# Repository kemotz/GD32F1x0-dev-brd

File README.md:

# GD32F1x0-dev-brd
 
GigaDevice GD32F1x0 value line MCU development board. The board supports F130/150/170/190 however the assembly files are created for F190 using JLCPCB service.

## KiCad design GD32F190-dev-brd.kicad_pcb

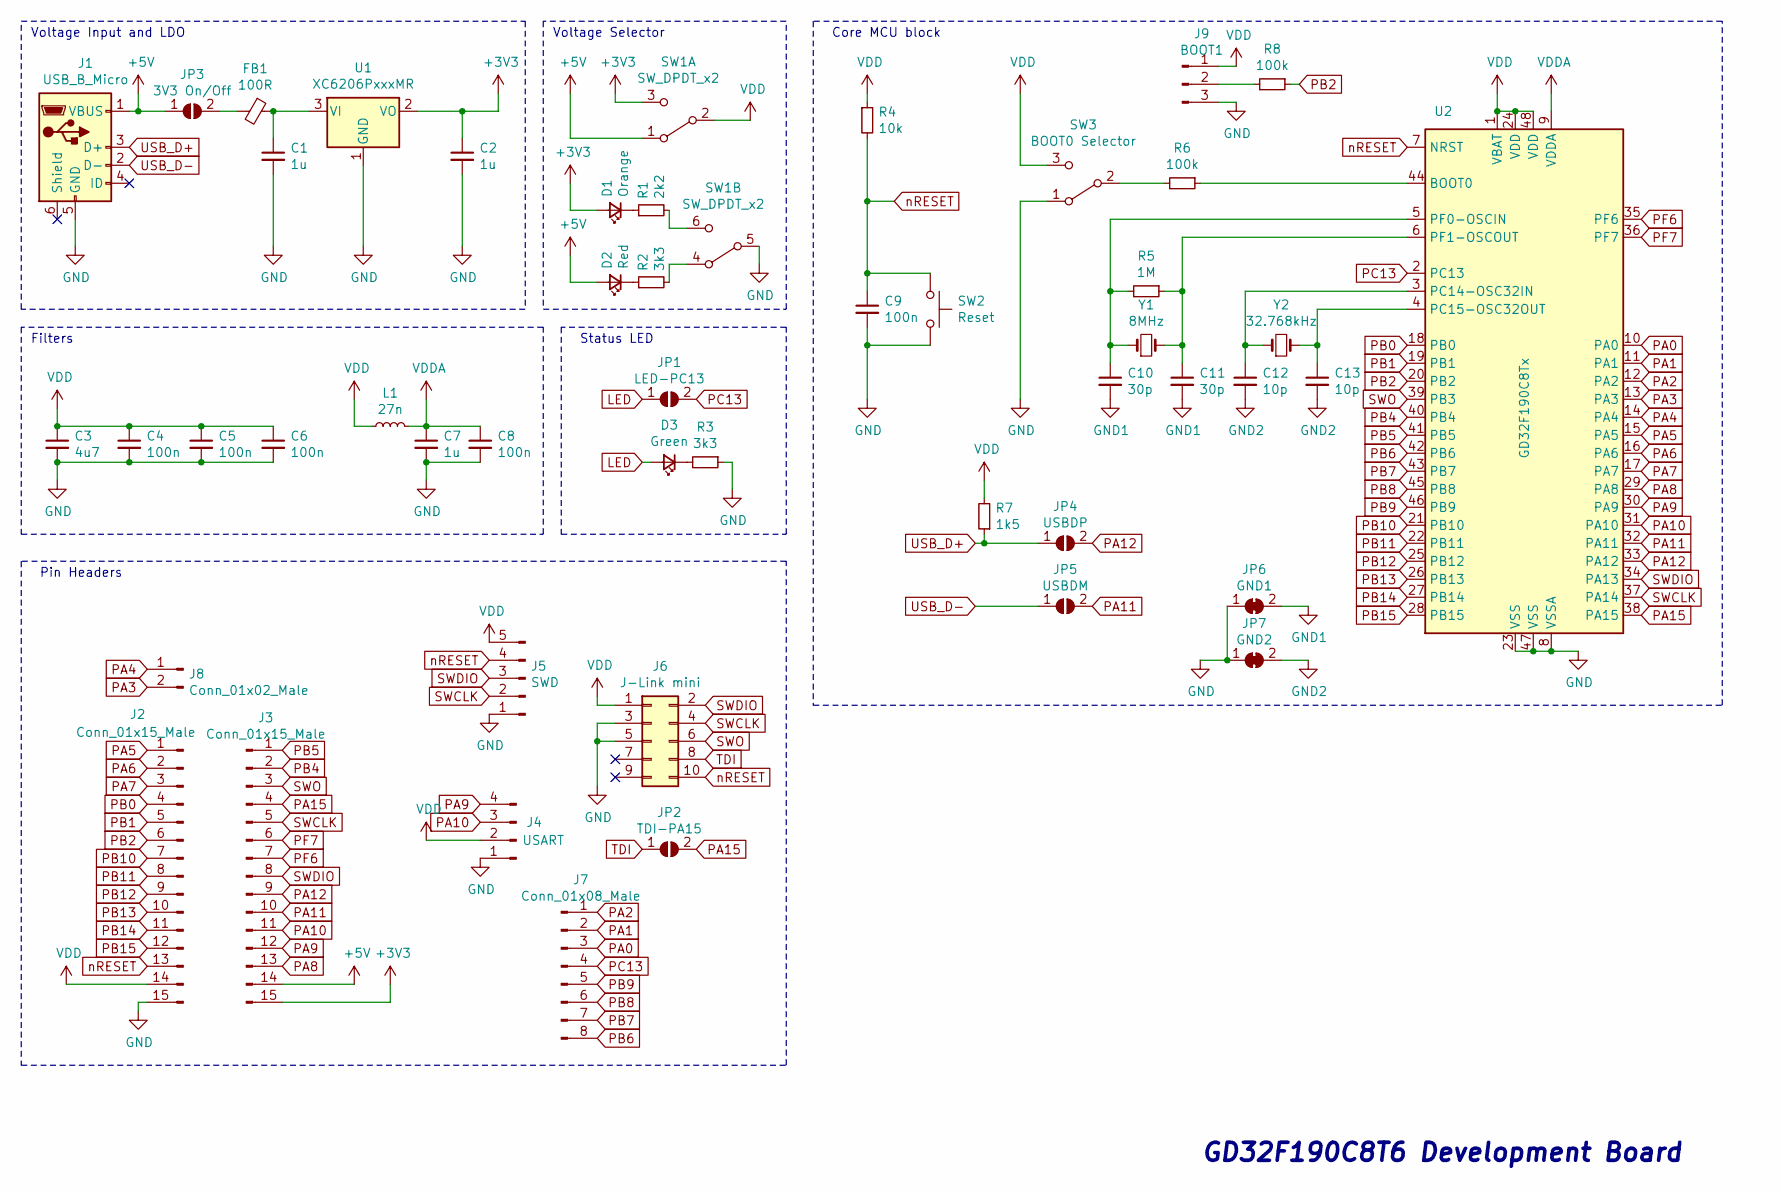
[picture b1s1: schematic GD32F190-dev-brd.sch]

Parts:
C1, C2, C7: 1u; C_0603_1608Metric
C3: 4u7; C_0402_1005Metric
C4, C5, C6: 100n; C_0402_1005Metric
C8, C9: 100n; C_0603_1608Metric
C10, C11: 30p; C_0603_1608Metric
C12, C13: 10p; C_0603_1608Metric
D1: Orange; LED_0603_1608Metric
D2: Red; LED_0603_1608Metric
D3: Green; LED_0603_1608Metric
FB1: 100R; L_0805_2012Metric
J1: USB_B_Micro; USB_Micro-B_MicroQTJ
J2, J3: Conn_01x15_Male; PinHeader_1x15_P2.54mm_Vertical
J4: USART; PinHeader_1x04_P2.54mm_Vertical
J5: SWD; PinHeader_1x05_P2.54mm_Vertical
J6: J-Link mini; PinHeader_2x05_P1.27mm_Vertical
J7: Conn_01x08_Male; PinHeader_1x08_P2.54mm_Vertical
J8: Conn_01x02_Male; PinHeader_1x02_P2.54mm_Vertical
J9: BOOT1; PinHeader_1x03_P2.54mm_Vertical
JP1: LED-PC13; SolderJumper-2_P1.3mm_Open_RoundedPad1.0x1.5mm
JP2: TDI-PA15; SolderJumper-2_P1.3mm_Open_RoundedPad1.0x1.5mm
JP3: 3V3 On/Off; SolderJumper-2_P1.3mm_Open_RoundedPad1.0x1.5mm
JP4: USBDP; SolderJumper-2_P1.3mm_Open_RoundedPad1.0x1.5mm
JP5: USBDM; SolderJumper-2_P1.3mm_Open_RoundedPad1.0x1.5mm
JP6: GND1; GND-bridge
JP7: GND2; GND-bridge
L1: 27n; L_0603_1608Metric
R1: 2k2; R_0603_1608Metric
R2, R3: 3k3; R_0603_1608Metric
R4: 10k; R_0603_1608Metric
R5: 1M; R_0603_1608Metric
R6, R8: 100k; R_0603_1608Metric
R7: 1k5; R_0603_1608Metric
SW1: SW_DPDT_x2; SK22H03
SW2: Reset; SW_SPST_PTS810
SW3: BOOT0 Selector; SK22H03
U1: XC6206PxxxMR; SOT-23
U2: GD32F190C8Tx; LQFP-48_7x7mm_P0.5mm
Y1: 8MHz; Crystal_SMD_5032-2Pin_5.0x3.2mm
Y2: 32.768kHz; Crystal_SMD_3215-2Pin_3.2x1.5mm

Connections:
+3V3: C2.1, D1.2 (A), J3.15, SW1.3 (C), U1.2 (VO)
+5V: D2.2 (A), J1.1 (VBUS), J3.14, JP3.1 (A), SW1.1 (A)
GND: C1.2, C2.2, C3.2, C4.2, C5.2, C6.2, C7.2, C8.2, C9.2, J1.5 (GND), J2.15, J4.1, J5.1, J6.3, J6.5, J9.3, JP6.1 (A), JP7.1 (A), R3.1, SW1.5 (B), SW2.2, SW3.1 (A), U1.1 (GND), U2.8 (VSSA), U2.23 (VSS), U2.47 (VSS)
GND1: C10.2, C11.2, JP6.2 (B)
GND2: C12.2, C13.2, JP7.2 (B)
LED: D3.2 (A), JP1.1 (A)
unnamed: C1.1, FB1.1, U1.3 (VI)
unnamed: C10.1, R5.2, U2.5 (PF0-OSCIN), Y1.1
unnamed: C11.1, R5.1, U2.6 (PF1-OSCOUT), Y1.2
unnamed: C12.1, U2.3 (PC14-OSC32IN), Y2.1
unnamed: C13.1, U2.4 (PC15-OSC32OUT), Y2.2
unnamed: D1.1 (K), R1.1
unnamed: D2.1 (K), R2.1
unnamed: D3.1 (K), R3.2
unnamed: FB1.2, JP3.2 (B)
unnamed: J9.2, R8.2
unnamed: R1.2, SW1.6 (C)
unnamed: R2.2, SW1.4 (A)
unnamed: R6.1, U2.44 (BOOT0)
unnamed: R6.2, SW3.2 (B)
PA0: J7.3, U2.10 (PA0)
PA1: J7.2, U2.11 (PA1)
PA2: J7.1, U2.12 (PA2)
PA3: J8.2, U2.13 (PA3)
PA4: J8.1, U2.14 (PA4)
PA5: J2.1, U2.15 (PA5)
PA6: J2.2, U2.16 (PA6)
PA7: J2.3, U2.17 (PA7)
PA8: J3.13, U2.29 (PA8)
PA9: J3.12, J4.4, U2.30 (PA9)
PA10: J3.11, J4.3, U2.31 (PA10)
PA11: J3.10, JP5.2 (B), U2.32 (PA11)
PA12: J3.9, JP4.2 (B), U2.33 (PA12)
PA15: J3.4, JP2.2 (B), U2.38 (PA15)
PB0: J2.4, U2.18 (PB0)
PB1: J2.5, U2.19 (PB1)
PB2: J2.6, R8.1, U2.20 (PB2)
PB4: J3.2, U2.40 (PB4)
PB5: J3.1, U2.41 (PB5)
PB6: J7.8, U2.42 (PB6)
PB7: J7.7, U2.43 (PB7)
PB8: J7.6, U2.45 (PB8)
PB9: J7.5, U2.46 (PB9)
PB10: J2.7, U2.21 (PB10)
PB11: J2.8, U2.22 (PB11)
PB12: J2.9, U2.25 (PB12)
PB13: J2.10, U2.26 (PB13)
PB14: J2.11, U2.27 (PB14)
PB15: J2.12, U2.28 (PB15)
PC13: J7.4, JP1.2 (B), U2.2 (PC13)
PF6: J3.7, U2.35 (PF6)
PF7: J3.6, U2.36 (PF7)
SWCLK: J3.5, J5.2, J6.4, U2.37 (PA14)
SWDIO: J3.8, J5.3, J6.2, U2.34 (PA13)
SWO: J3.3, J6.6, U2.39 (PB3)
TDI: J6.8, JP2.1 (A)
USB_D+: J1.3 (D+), JP4.1 (A), R7.1
USB_D-: J1.2 (D-), JP5.1 (A)
VDD: C3.1, C4.1, C5.1, C6.1, J2.14, J4.2, J5.5, J6.1, J9.1, L1.1, R4.1, R7.2, SW1.2 (B), SW3.3 (C), U2.1 (VBAT), U2.24 (VDD), U2.48 (VDD)
VDDA: C7.1, C8.1, L1.2, U2.9 (VDDA)
nRESET: C9.1, J2.13, J5.4, J6.10, R4.2, SW2.1, U2.7 (NRST)

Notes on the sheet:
Voltage Input and LDO
Voltage Selector
Filters
Core MCU block
Status LED
Pin Headers
GD32F190C8T6 Development Board

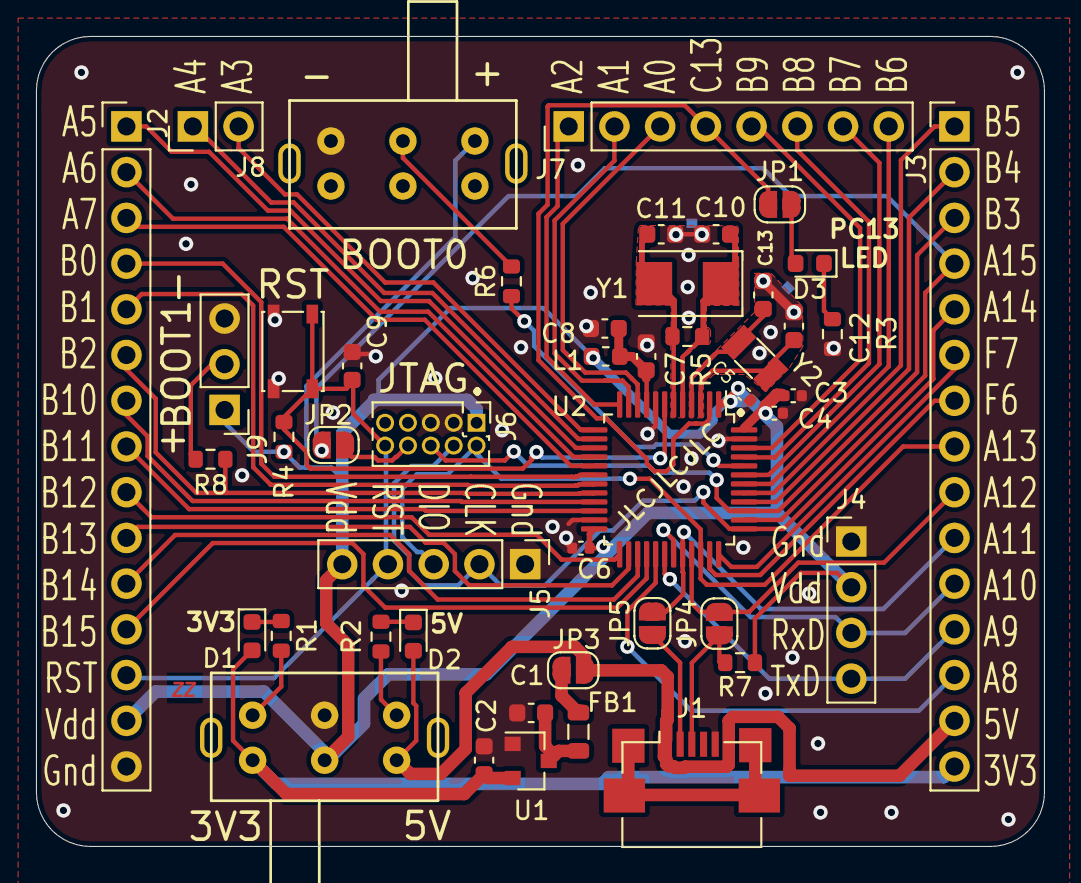
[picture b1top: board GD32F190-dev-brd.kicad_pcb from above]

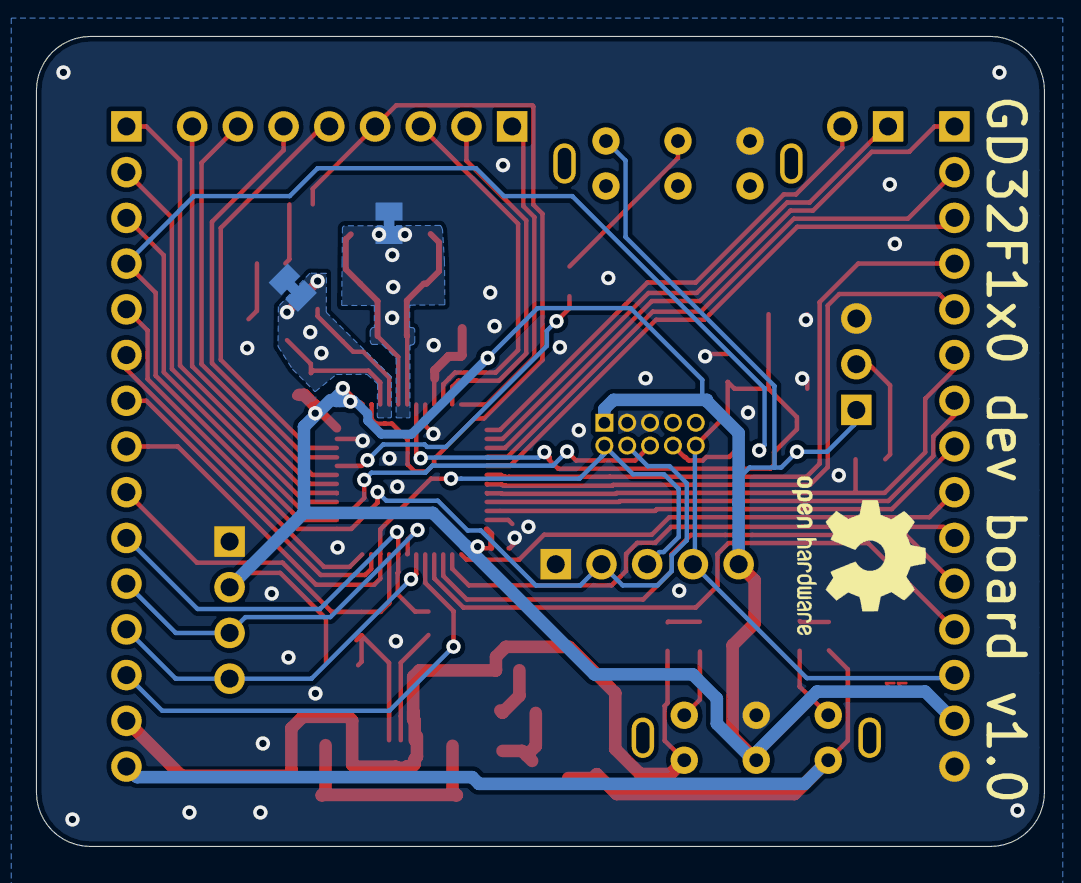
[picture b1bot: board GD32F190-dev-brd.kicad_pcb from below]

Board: 2 copper layers, 56.0 x 45.0 mm, 49 parts (2 on the bottom side), 61 nets.

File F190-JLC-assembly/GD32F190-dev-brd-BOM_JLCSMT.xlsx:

Comment | Designator | Footprint | LCSC Part #（optional）
1k5 | R7 | R_0603_1608Metric | C22843
1u | C1,C2,C7 | C_0603_1608Metric | C15849
100n | C8,C9 | C_0603_1608Metric | C14663
30p | C10,C11 | C_0603_1608Metric | C22397
10p | C12,C13 | C_0603_1608Metric | C1634
Orange | D1 | LED_0603_1608Metric | C72038
Red | D2 | LED_0603_1608Metric | C2286
Green | D3 | LED_0603_1608Metric | C72043
100R | FB1 | L_0805_2012Metric | C1015
27n | L1 | L_0603_1608Metric | C12100
2k2 | R1 | R_0603_1608Metric | C4190
3k3 | R2,R3 | R_0603_1608Metric | C22978
10k | R4 | R_0603_1608Metric | C25804
1M | R5 | R_0603_1608Metric | C22935
100k | R6,R8 | R_0603_1608Metric | C25803
XC6206PxxxMR | U1 | SOT-23 | C5446
GD32F190C8Tx | U2 | LQFP-48_7x7mm_P0.5mm | C84217
8MHz | Y1 | Crystal_SMD_5032-2Pin_5.0x3.2mm | C115962
32.768kHz | Y2 | Crystal_SMD_3215-2Pin_3.2x1.5mm | C32346
4u7 | C3 | C_0402_1005Metric | C23733
100n | C4,C5,C6 | C_0402_1005Metric | C1525
USB_B_Micro | J1 | USB_Micro-B_MicroQTJ | C404968

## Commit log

2021-06-10 v1.0 release
2021-06-10 added schematics in pdf format
2021-06-10 Revert "Merge branch 'main' of https://github.com/kemotz/GD32F1x0-dev-brd into main"
    This reverts commit b5d80814c696244c37bc7a8d1ae8db8ffd3dc419, reversing
    changes made to c61999284e8aaf820bb81bb67a56c585d303d18e.
2021-06-10 Revert "Revert "Merge branch 'main' of https://github.com/kemotz/GD32F1x0-dev-brd into main""
    This reverts commit 18c66b826cc2bfe1479a188c76804c46eb1ffb94.
